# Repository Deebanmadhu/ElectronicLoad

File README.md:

# ElectronicLoad
A device to simulate output Load profiles

The project File can be viewed through KICAD EDA software
.pro - KICAD project file
.sch - KICAD Schematic File
.pcb - KKICAD PCB file

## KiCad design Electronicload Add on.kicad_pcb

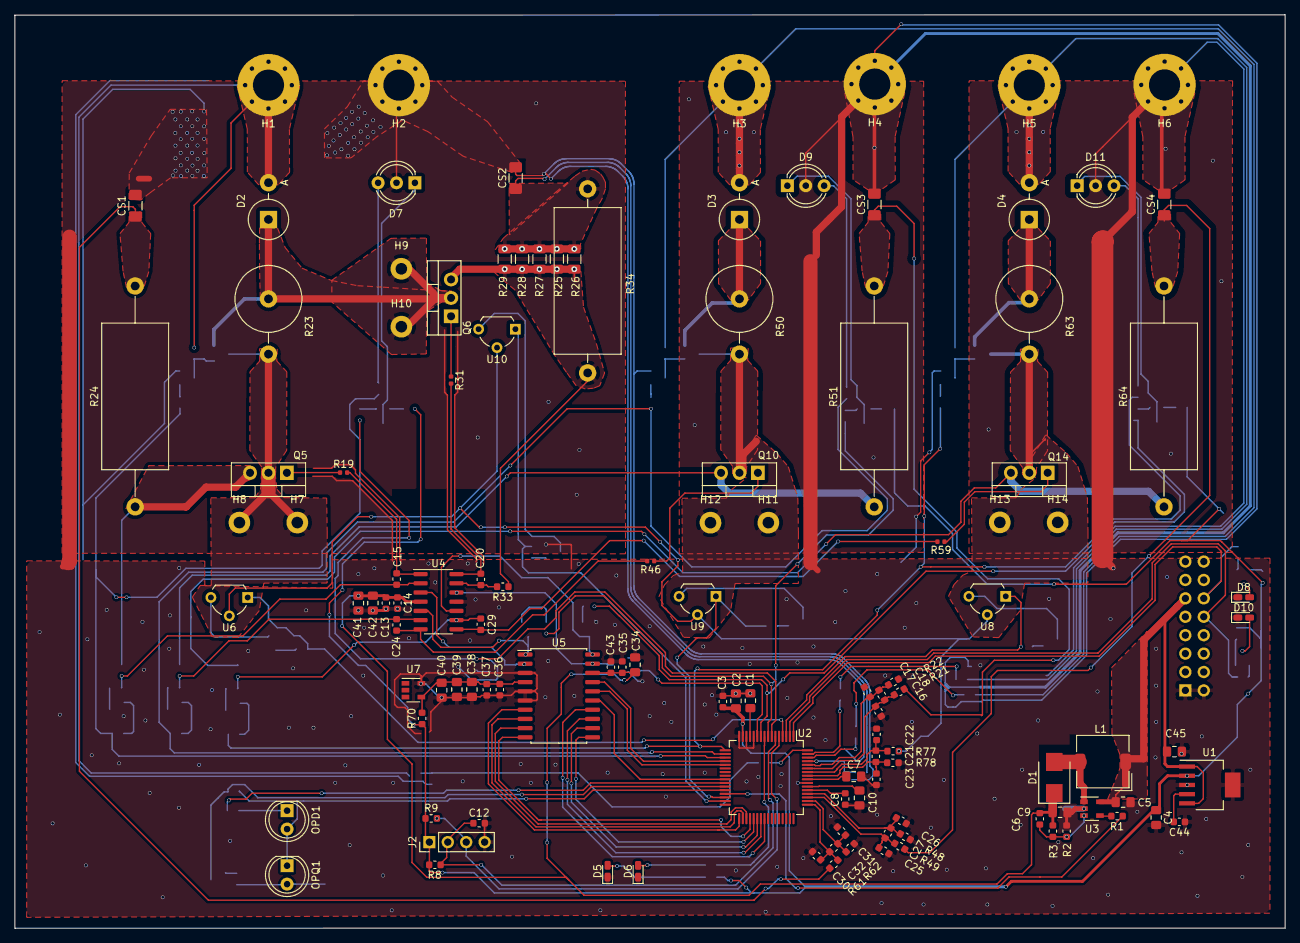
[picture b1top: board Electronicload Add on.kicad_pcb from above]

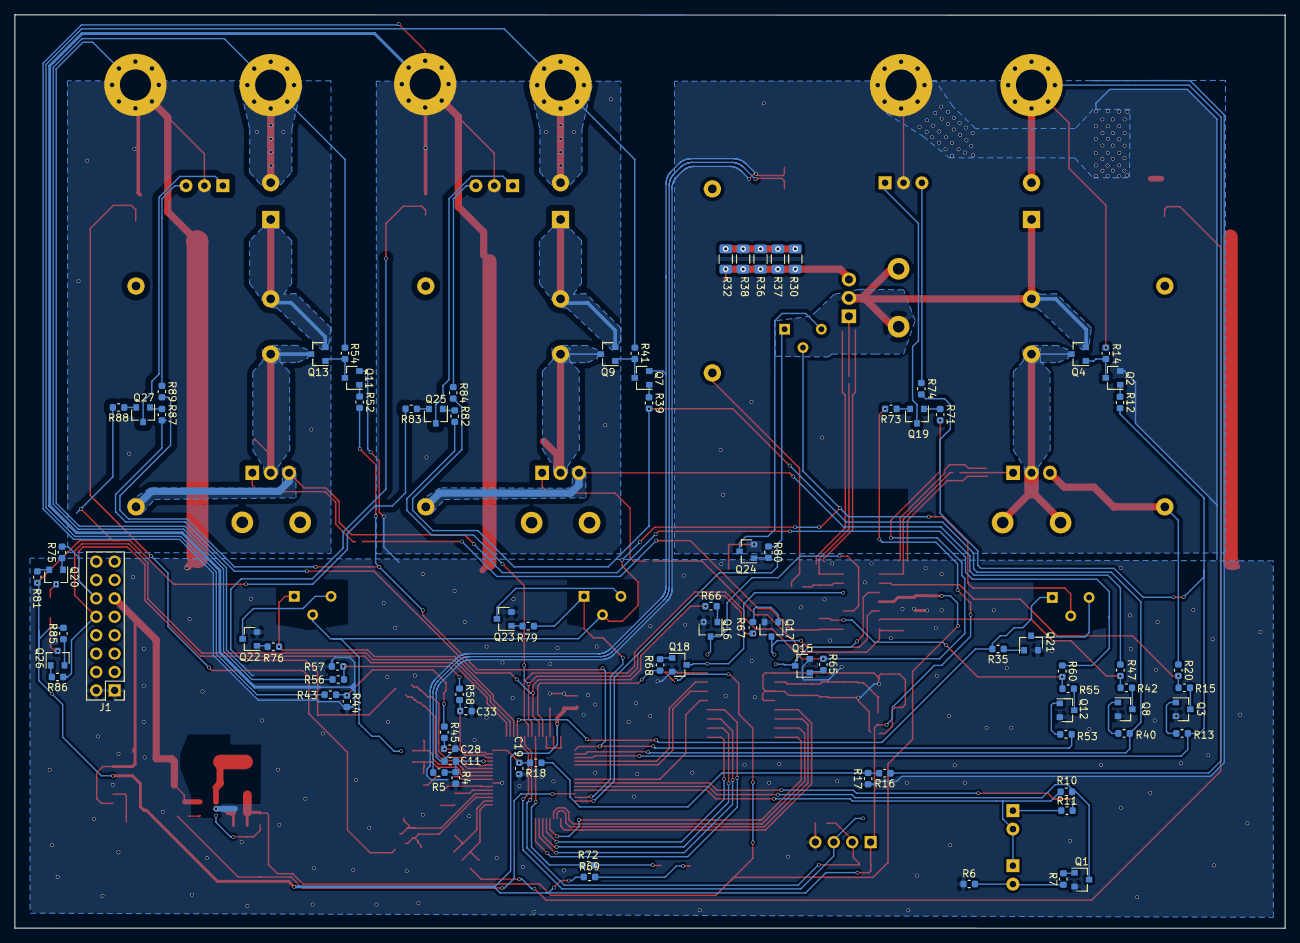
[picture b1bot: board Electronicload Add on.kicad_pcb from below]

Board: 2 copper layers, 175.3 x 126.1 mm, 205 parts (86 on the bottom side), 140 nets.

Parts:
C1, C2, C4, C5, C7, C8, C9, C34, C38, C39, C41, C45: 10uF; C_0805_2012Metric_Pad1.15x1.40mm_HandSolder
C3, C10, C12, C13, C37, C43: 0.1uF; C_0603_1608Metric
C6, C44: 220pF; C_0603_1608Metric
C11, C19, C28, C33: 1pF; C_0603_1608Metric
C14, C35, C36: 0.01uF; C_0603_1608Metric
C15, C20, C24, C29: op; C_0603_1608Metric
C16, C17, C22, C23, C25, C26, C30, C31: 33nF; C_0603_1608Metric
C18, C21, C27, C32: 15nF; C_0603_1608Metric
C40, C42: 1uF; C_0805_2012Metric_Pad1.15x1.40mm_HandSolder
CS1, CS2, CS3, CS4: R; R_1206_3216Metric_Pad1.42x1.75mm_HandSolder
D1: B1100-13-F; D_SMB
D2, D3, D4: SB560; D_DO-27_P5.08mm_Vertical_AnodeUp
D5: Power; LED_0603_1608Metric_Castellated
D6: ~Fault~; LED_0603_1608Metric_Castellated
D7, D9, D11: LED_Dual_ACA; LED_D5.0mm-3
D8: LED1; LED_0603_1608Metric_Castellated
D10: LED2; LED_0603_1608Metric_Castellated
H1, H2, H3, H4, H5, H6: MountingHole_Pad; MountingHole_4.3mm_M4_Pad_Via
H7, H8, H9, H10, H11, H12, H13, H14: HS_Pad; MountingHole_2.2mm_M2_Pad
J1: Conn_02x08_Odd_Even; PinHeader_2x08_P2.54mm_Vertical
J2: Conn_01x04; PinHeader_1x04_P2.54mm_Vertical
L1: 6.8uH; L_TDK_SLF7055
OPD1: D_Photo; LED_D5.0mm_IRGrey
OPQ1: Q_Photo_NPN; LED_D5.0mm_IRGrey
Q1: MMBT2222; SOT-23
Q2, Q3, Q7, Q8, Q11, Q12, Q15, Q16, Q17, Q18, Q21, Q22, Q23, Q24: ZVN4106F; SOT-23
Q4, Q9, Q13, Q19, Q20, Q25, Q26, Q27: NXP2301P; SOT-23
Q5, Q6, Q10, Q14: CSD17527Q5A; TO-220-3_Vertical
R1, R5: 47k; R_0603_1608Metric
R2: 15k; R_0603_1608Metric
R3: 150k; R_0603_1608Metric
R4, R33: 0R; R_0603_1608Metric
R6, R11: 510R; R_0603_1608Metric
R7, R8, R9, R10: 10k; R_0603_1608Metric
R12, R13, R14, R16, R35, R39, R40, R41, R43, R52, R53, R54, R56, R65, R66, R67, R68, R76, R79, R80: 100k; R_0603_1608Metric
R15, R17, R20, R42, R44, R47, R55, R57, R60: 1k; R_0603_1608Metric
R18, R45, R58: 30k; R_0603_1608Metric
R19, R31, R46, R59: 5.1R; R_0402_1005Metric
R21, R22, R48, R49, R61, R62, R77, R78: 220R; R_0603_1608Metric
R23, R50, R63: 10R; R_Axial_DIN0922_L20.0mm_D9.0mm_P7.62mm_Vertical
R24, R51, R64: 5R; R_Axial_DIN0922_L20.0mm_D9.0mm_P30.48mm_Horizontal
R25, R26, R27, R28, R29, R30, R32, R36, R37, R38: 10R; R_1206_3216Metric
R34: nm; R_Axial_DIN0922_L20.0mm_D9.0mm_P25.40mm_Horizontal
R69: 24k; R_0603_1608Metric
R70: R; R_0603_1608Metric
R71, R75, R82, R86, R87: 100K; R_0603_1608Metric
R72, R73, R74, R81, R83, R84, R85, R88, R89: 2k; R_0603_1608Metric
U1: TPS73733; SOT-223-6
U2: RL78/I1C -64pin; LQFP-64_10x10mm_P0.5mm
U3: LM2731XMF; SOT-23-5
U4: TLV9104; SOIC-14_3.9x8.7mm_P1.27mm
U5: TLC7226; SOIC-20W_7.5x12.8mm_P1.27mm
U6, U8, U9, U10: LM60; TO-92L_Wide
U7: LM4030-2.5; SOT-23-5

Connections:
5.2V: C5.2, C45.1, J1.11, L1.1, U1.1, U1.5, U3.5
+3V3: C2.1, C3.2, C4.1, J2.1, R8.1, R9.1, R69.1, R70.1, R73.2, R81.2, R83.2, R85.2, R88.2, U1.2, U2.15
+12V: C6.1, C9.1, C13.2, C14.1, C34.2, C35.1, C41.2, C42.2, C43.1, D1.1, R3.1, U4.4, U5.18
A0: U2.20, U5.17
A1: U2.21, U5.16
A_TEMP: R35.2, U2.4, U6.1
BOOST_ENABLE: R1.1, U2.29
B_TEMP: R76.2, U2.3, U8.1
CH1_HP: R12.2, R13.2, R74.2, U2.19
CH1_V: C19.1, R18.2, U2.64
CH2_HP: R39.2, R40.2, R84.2, U2.18
CH2_V: C28.1, R45.2, U2.62
CH3_HP: R52.2, R53.2, R89.2, U2.17
CH3_V: C33.1, R58.2, U2.63
C_TEMP: R79.2, U2.30, U9.1
DB0: U2.40, U5.14
DB1: U2.39, U5.13
DB2: U2.38, U5.12
DB3: U2.37, U5.11
DB4: U2.36, U5.10
DB5: U2.35, U5.9
DB6: U2.34, U5.8
DB7: U2.33, U5.7
D_TEMP: R80.2, U2.31, U10.1
GND: C1.1, C2.2, C3.1, C4.2, C5.1, C7.1, C8.1, C9.2, C10.1, C11.2, C12.2, C13.1, C14.2, C16.1, C17.2, C19.2, C22.2, C23.1, C25.1, C26.2, C28.2, C30.1, C31.2, C33.2, C34.1, C35.2, C36.1, C37.2, C38.2, C39.2, C40.2, C41.1, C42.1, C43.2, C44.1, C45.2, CS1.1, CS2.2, CS3.2, CS4.2, D5.1, D6.1, D7.2, D8.1, D9.2, D10.1, D11.2, H2.1, H4.1, H6.1, J1.1, J1.2, J2.4, Q1.2, Q2.2, Q3.2, Q7.2, Q8.2, Q11.2, Q12.2, Q15.2, Q16.2, Q17.2, Q18.2, Q21.2, Q22.2, Q23.2, Q24.2, R2.2, R4.2, R6.1, R17.1, R22.1, R44.1, R49.1, R57.1, R62.1, R78.1, U1.3, U1.6, U2.12, U2.14, U2.16, U2.55, U3.2, U4.11, U5.3, U5.5, U5.6, U7.5
I_CH1N: C31.1, C32.2, R62.2, U2.50
I_CH1P: C30.2, C32.1, R61.2, U2.49
I_CH1_T: CS2.1, R5.2, R25.2, R26.2, R27.2, R28.2, R29.2, R30.2, R32.2, R34.2, R36.2, R37.2, R38.2
I_CH2N: C17.1, C18.2, R22.2, U2.60
I_CH2P: C16.2, C18.1, R21.2, U2.59
I_CH3N: C26.1, C27.2, R49.2, U2.52
I_CH3P: C25.2, C27.1, R48.2, U2.51
LOADCH1: D2.2, H1.1, R14.2, R16.1
LOADCH2: D3.2, H3.1, R41.2, R43.1
LOADCH3: D4.2, H5.1, R54.2, R56.1
unnamed: C1.2, U2.13
unnamed: C6.2, R2.1, R3.2, U3.3
unnamed: C7.2, U2.56
unnamed: C8.2, U2.54
unnamed: C10.2, U2.53
unnamed: C11.1, R4.1, R5.1, U2.61
unnamed: C15.1, R19.2, U4.1
unnamed: C15.2, R15.2, R20.2, U4.2
unnamed: C20.1, R31.2, U4.14
unnamed: C20.2, R33.2, U4.13
unnamed: C24.1, R46.2, U4.7
unnamed: C24.2, R42.2, R47.2, U4.6
unnamed: C29.1, R59.2, U4.8
unnamed: C29.2, R55.2, R60.2, U4.9
unnamed: C44.2, U1.4
unnamed: CS1.2, R24.2, R61.1
unnamed: CS3.1, R21.1, R51.2
unnamed: CS4.1, R48.1, R64.2
unnamed: D1.2, L1.2, U3.1
unnamed: D2.1, H9.1, H10.1, Q4.2, Q6.2, R23.1
unnamed: D3.1, Q9.2, R50.1
unnamed: D4.1, Q13.2, R63.1
unnamed: D5.2, R69.2
unnamed: D6.2, R72.2
unnamed: D7.1, Q19.3
unnamed: D7.3, R74.1
unnamed: D8.2, Q20.3
unnamed: D9.1, Q25.3
unnamed: D9.3, R84.1
unnamed: D10.2, Q26.3
unnamed: D11.1, Q27.3
unnamed: D11.3, R89.1
unnamed: H7.1, H8.1, Q4.3, Q5.2, R23.2
unnamed: H11.1, H12.1, Q9.3, Q10.2, R50.2
unnamed: H13.1, H14.1, Q13.3, Q14.2, R63.2
unnamed: OPD1.1, R11.2
unnamed: OPQ1.2, R6.2, R7.1
unnamed: Q1.1, R7.2
unnamed: Q2.1, R12.1
unnamed: Q2.3, Q4.1, R14.1
unnamed: Q3.1, R13.1
unnamed: Q3.3, R15.1
unnamed: Q5.1, R19.1
unnamed: Q5.3, R20.1, R24.1
unnamed: Q6.1, R31.1
unnamed: Q6.3, R25.1, R26.1, R27.1, R28.1, R29.1, R30.1, R32.1, R33.1, R34.1, R36.1, R37.1, R38.1
unnamed: Q7.1, R39.1
unnamed: Q7.3, Q9.1, R41.1
unnamed: Q8.1, R40.1
unnamed: Q8.3, R42.1
unnamed: Q10.1, R46.1
unnamed: Q10.3, R47.1, R51.1
unnamed: Q11.1, R52.1
unnamed: Q11.3, Q13.1, R54.1
unnamed: Q12.1, R53.1
unnamed: Q12.3, R55.1
unnamed: Q14.1, R59.1
unnamed: Q14.3, R60.1, R64.1
unnamed: Q15.1, R65.1
unnamed: Q16.1, R66.1
unnamed: Q17.1, R67.1
unnamed: Q18.1, R68.1
unnamed: Q19.1, R71.1
unnamed: Q19.2, R73.1
unnamed: Q20.1, R75.1
unnamed: Q20.2, R81.1
unnamed: Q21.1, R35.1
unnamed: Q21.3, U6.3
unnamed: Q22.1, R76.1
unnamed: Q22.3, U8.3
unnamed: Q23.1, R79.1
unnamed: Q23.3, U9.3
unnamed: Q24.1, R80.1
unnamed: Q24.3, U10.3
unnamed: Q25.1, R82.1
unnamed: Q25.2, R83.1
unnamed: Q26.1, R86.2
unnamed: Q26.2, R85.1
unnamed: Q27.1, R87.1
unnamed: Q27.2, R88.1
unnamed: R1.2, U3.4
unnamed: R16.2, R17.2, R18.1
unnamed: R43.2, R44.2, R45.1
unnamed: R56.2, R57.2, R58.1
OPRX: Q1.3, R10.1, U2.27
OPTX: R11.1, U2.26
OPW: OPD1.2, OPQ1.1, R10.2, U2.28
RXD: J1.10, R86.1, U2.2
TEMP_N: C21.1, C23.2, R78.2, U2.57
TEMP_P: C21.2, C22.1, R77.2, U2.58
TOOL: J2.3, R9.2, U2.5
TXD: J1.12, R75.2, U2.1
Temperature: R77.1, U6.2, U8.2, U9.2, U10.2
VREF: C36.2, C37.1, C38.1, C39.1, C40.1, R70.2, U5.4, U7.4
Vouta_zero: R65.2, R71.2, U2.7
Voutb_zero: R67.2, R82.2, U2.8
Voutc_zero: R66.2, R87.2, U2.10
Voutd_zero: R68.2, U2.11
vout_A: Q15.3, U4.3, U5.2
vout_B: Q17.3, U4.5, U5.1
vout_C: Q16.3, U4.10, U5.20
vout_D: Q18.3, U4.12, U5.19
~FAULT: R72.1, U2.9
~RESET: C12.1, J2.2, R8.2, U2.6
~WR: U2.25, U5.15
